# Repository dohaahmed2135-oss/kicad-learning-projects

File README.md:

# KiCad Learning Projects

Welcome to my **KiCad Learning Projects** repository!

This repository documents my journey of learning **PCB design** using KiCad through a series of practical hardware projects. Each project has helped me build a stronger understanding of schematic design, PCB layout, component placement, routing, and hardware documentation.

---

## Skills Developed

* Schematic Capture
* PCB Layout & Routing
* Component & Footprint Selection
* Electrical Rule Check (ERC)
* Design Rule Check (DRC)
* Power & Signal Routing
* PCB Visualization
* Embedded Hardware Design
* GitHub

---

# Projects

## 01 - 12V AC to DC Converter

Designed a PCB for converting AC voltage to a regulated DC output while learning the complete PCB design workflow in KiCad.

<table>
<tr>
<td align="center">
<br>
<b>PCB Layout</b>
</td>

<td align="center">
<br>
<b>3D Front View</b>
</td>
</tr>
</table>

---

## 02 - Motor Driver

Designed a motor driver PCB to practice component placement, power routing, and PCB organization for embedded applications.

<table>
<tr>
<td align="center">
<br>
<b>PCB Layout</b>
</td>

<td align="center">
<br>
<b>3D Front View</b>
</td>
</tr>
</table>

---

## 03 - STM32 GPS Tracker with SIM808

Designed an STM32-based GPS tracking PCB integrating the SIM808 GSM/GPRS and GPS module.

<table>
<tr>
<td align="center">
<br>
<b>PCB Front Layout</b>
</td>

<td align="center">
<br>
<b>3D Front View</b>
</td>
</tr>
</table>

---

## 04 - STM32 Bluetooth 

Designed a custom STM32 Bluetooth development board to gain experience with wireless embedded hardware design. This project focused on Bluetooth module integration, PCB placement, routing, and overall board organization.

<table>
<tr>
<td align="center">
<br>
<b>PCB Layout</b>
</td>

<td align="center">
<br>
<b>3D Front View</b>
</td>
</tr>
</table>

---

## 05 - ESP32 S3 IOT Testboard

Designed a four-layer ESP32-S3 IoT development board featuring sensor interfaces and a QWIIC connector. This project provided practical experience with multilayer PCB design, power distribution, and high-density routing techniques.

<table>
<tr>
<td align="center">
<br>
<b>PCB Front Layout</b>
</td>

<td align="center">
<br>
<b>3D Front View</b>
</td>
</tr>
</table>

# Learning Goal

The purpose of this repository is to document my progress in PCB design while building a strong foundation in embedded systems and hardware engineering.

My long-term goal is to design complete embedded and robotics systems by combining PCB design, embedded software, CAD, and robotics.

# Acknowledgements

The projects in this repository were completed as part of my PCB design learning journey using the following educational resources:

Ampnics – Master KiCad With Projects (Projects 01–03)

Phil's Lab – KiCad 7 STM32 Bluetooth Hardware Design (Project 04)

KiCad 9: Design an ESP32-S3 IoT 4-layer PCB with Sensor and QWIIC Interface – Complete Guide (Project 05)

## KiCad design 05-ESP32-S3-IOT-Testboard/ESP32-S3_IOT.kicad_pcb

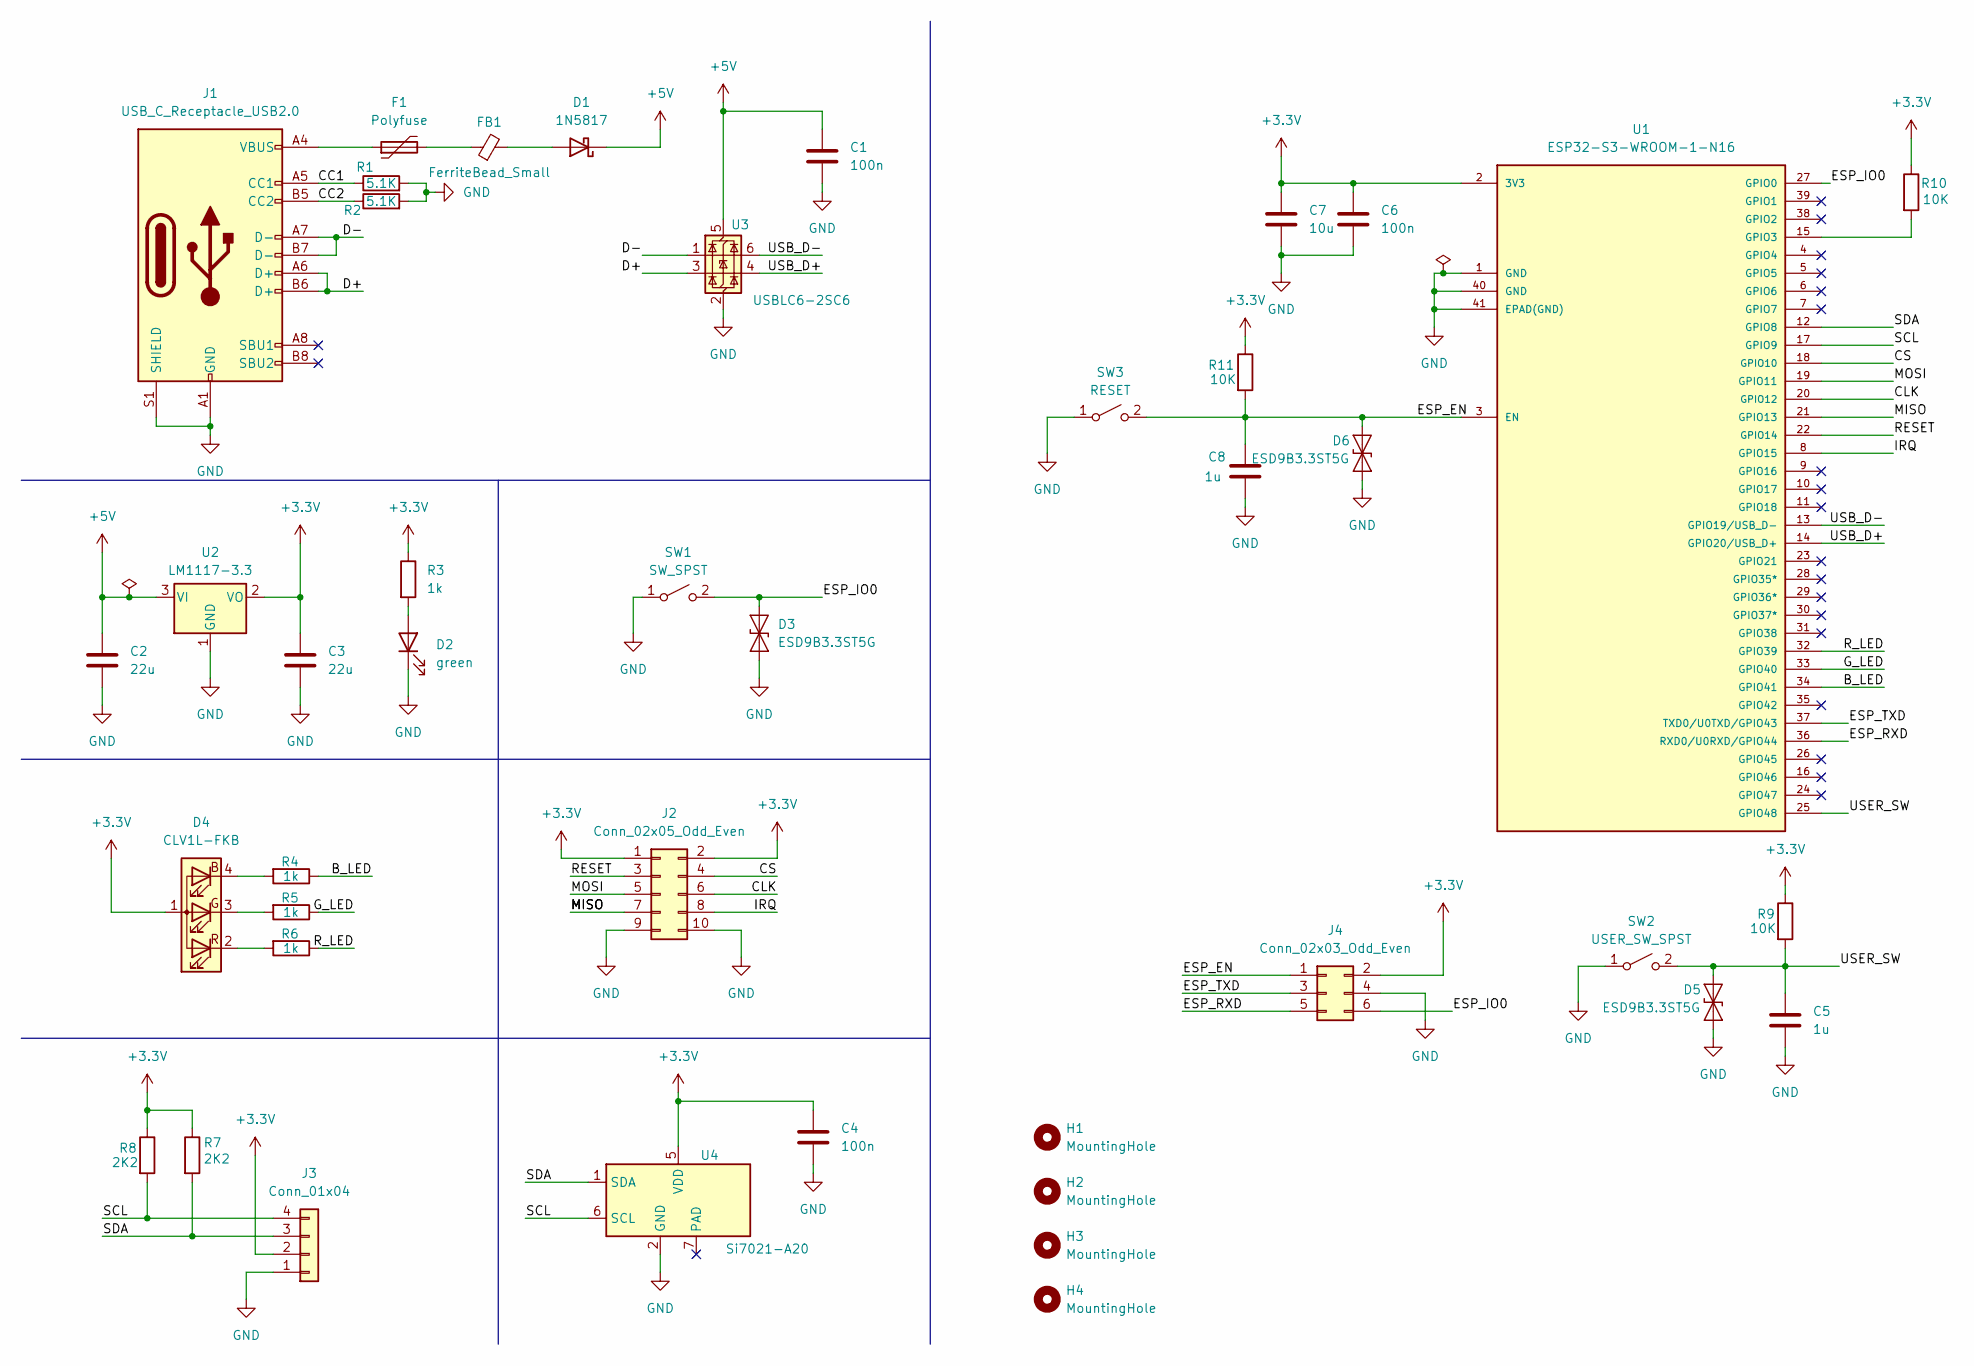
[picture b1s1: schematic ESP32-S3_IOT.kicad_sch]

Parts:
C1, C4, C6: 100n; C_0402_1005Metric_Pad0.74x0.62mm_HandSolder
C2, C3: 22u; C_0805_2012Metric
C5, C8: 1u; C_0603_1608Metric
C7: 10u; C_0603_1608Metric
D1: 1N5817; D_SOD-123
D2: green; LED_0603_1608Metric
D3, D5, D6: ESD9B3.3ST5G; D_SOD-923
D4: CLV1L-FKB; LED_Cree-PLCC4_3.2x2.8mm_CCW
F1: Polyfuse; Fuse_1206_3216Metric
FB1: FerriteBead_Small; L_0805_2012Metric
H1, H2, H3, H4: MountingHole; MountingHole_3.2mm_M3
J1: USB_C_Receptacle_USB2.0; USB_C_Receptacle_HRO_TYPE-C-31-M-12
J2: Conn_02x05_Odd_Even; PinHeader_2x05_P2.54mm_Vertical
J3: Conn_01x04; JST_XH_S4B-XH-A-1_1x04_P2.50mm_Horizontal
J4: Conn_02x03_Odd_Even; PinHeader_2x03_P2.54mm_Vertical
R1, R2: 5.1K; R_0402_1005Metric
R3, R4, R5, R6: 1k; R_0402_1005Metric
R7, R8: 2K2; R_0402_1005Metric
R9, R10, R11: 10K; R_0402_1005Metric
SW1: SW_SPST; SW_SPST_B3U-1000P
SW2: USER_SW_SPST; SW_Tactile_SPST_Angled_PTS645Vx31-2LFS
SW3: RESET; SW_SPST_B3U-1000P
U1: ESP32-S3-WROOM-1-N16; ESP32-S3-WROOM-1
U2: LM1117-3.3; SOT-223-3_TabPin2
U3: USBLC6-2SC6; SOT-23-6
U4: Si7021-A20; DFN-6-1EP_3x3mm_P1mm_EP1.5x2.4mm

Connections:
+3.3V: C3.1, C4.1, C6.1, C7.1, D4.1 (A), J2.1, J2.2, J3.2, J4.2, R3.1, R7.1, R8.1, R9.1, R10.1, R11.1, U1.2 (3V3), U2.2 (VO), U4.5 (VDD)
+5V: C1.1, C2.1, D1.1 (K), U2.3 (VI), U3.5 (VBUS)
/B_LED: R4.1, U1.34 (GPIO41)
/CC1: J1.A5 (CC1), R1.1
/CC2: J1.B5 (CC2), R2.1
/CLK: J2.6, U1.20 (GPIO12)
/CS: J2.4, U1.18 (GPIO10)
/D+: J1.A6 (D+), J1.B6 (D+), U3.3 (I/O2)
/D-: J1.A7 (D-), J1.B7 (D-), U3.1 (I/O1)
/ESP_EN: C8.1, D6.2 (A2), J4.1, R11.2, SW3.2 (B), U1.3 (EN); also elsewhere on the board
/ESP_IO0: D3.2 (A2), J4.6, SW1.2 (B), U1.27 (GPIO0); also elsewhere on the board
/ESP_RXD: J4.5, U1.36 (RXD0/U0RXD/GPIO44)
/ESP_TXD: J4.3, U1.37 (TXD0/U0TXD/GPIO43)
/G_LED: R5.1, U1.33 (GPIO40)
/IRQ: J2.8, U1.8 (GPIO15)
/MISO: J2.7, U1.21 (GPIO13)
/MOSI: J2.5, U1.19 (GPIO11)
/RESET: J2.3, U1.22 (GPIO14)
/R_LED: R6.1, U1.32 (GPIO39)
/SCL: J3.4, R8.2, U1.17 (GPIO9), U4.6 (SCL)
/SDA: J3.3, R7.2, U1.12 (GPIO8), U4.1 (SDA)
/USB_D+: U1.14 (GPIO20/USB_D+), U3.4 (I/O2)
/USB_D-: U1.13 (GPIO19/USB_D-), U3.6 (I/O1)
/USER_SW: C5.1, D5.2 (A2), R9.2, SW2.2 (B), U1.25 (GPIO48); also elsewhere on the board
GND: C1.2, C2.2, C3.2, C4.2, C5.2, C6.2, C7.2, C8.2, D2.1 (K), D3.1 (A1), D5.1 (A1), D6.1 (A1), J1.A1 (GND), J1.A12 (GND), J1.B1 (GND), J1.B12 (GND), J1.S1 (SHIELD), J2.9, J2.10, J3.1, J4.4, R1.2, R2.2, SW1.1 (A), SW2.1 (A), SW3.1 (A), U1.1 (GND), U1.40 (GND), U1.41 (EPAD(GND)), U2.1 (GND), U3.2 (GND), U4.2 (GND); also elsewhere on the board
unnamed: D1.2 (A), FB1.2
unnamed: D2.2 (A), R3.2
unnamed: D4.4 (BK), R4.2
unnamed: D4.3 (GK), R5.2
unnamed: D4.2 (RK), R6.2
unnamed: F1.1, J1.A4 (VBUS), J1.A9 (VBUS), J1.B4 (VBUS), J1.B9 (VBUS)
unnamed: F1.2, FB1.1
unnamed: R10.2, U1.15 (GPIO3)

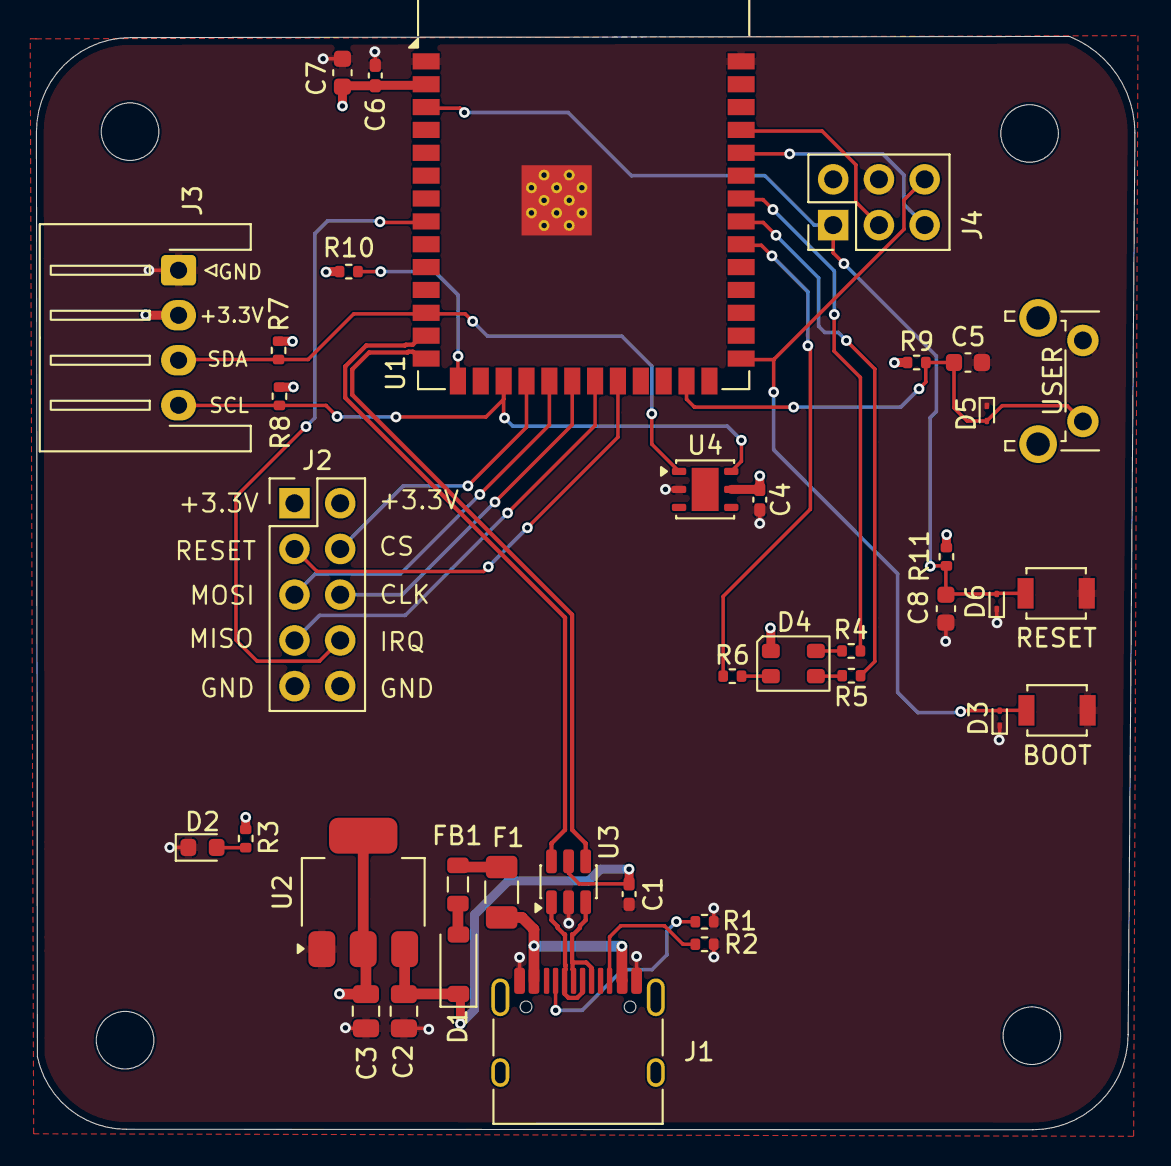
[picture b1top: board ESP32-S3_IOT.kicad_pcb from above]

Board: 4 copper layers, 61.0 x 60.7 mm, 42 parts (0 on the bottom side), 33 nets.

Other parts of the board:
BOOT: SW_SPST; SW_SPST_B3U-1000P
RESET: RESET; SW_SPST_B3U-1000P
USER: USER_SW_SPST; SW_Tactile_SPST_Angled_PTS645Vx31-2LFS

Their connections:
/ESP_EN: RESET.2 (B); also elsewhere on the board
/ESP_IO0: BOOT.2 (B); also elsewhere on the board
/USER_SW: USER.2 (B); also elsewhere on the board
GND: BOOT.1 (A), RESET.1 (A), USER.1 (A); also elsewhere on the board

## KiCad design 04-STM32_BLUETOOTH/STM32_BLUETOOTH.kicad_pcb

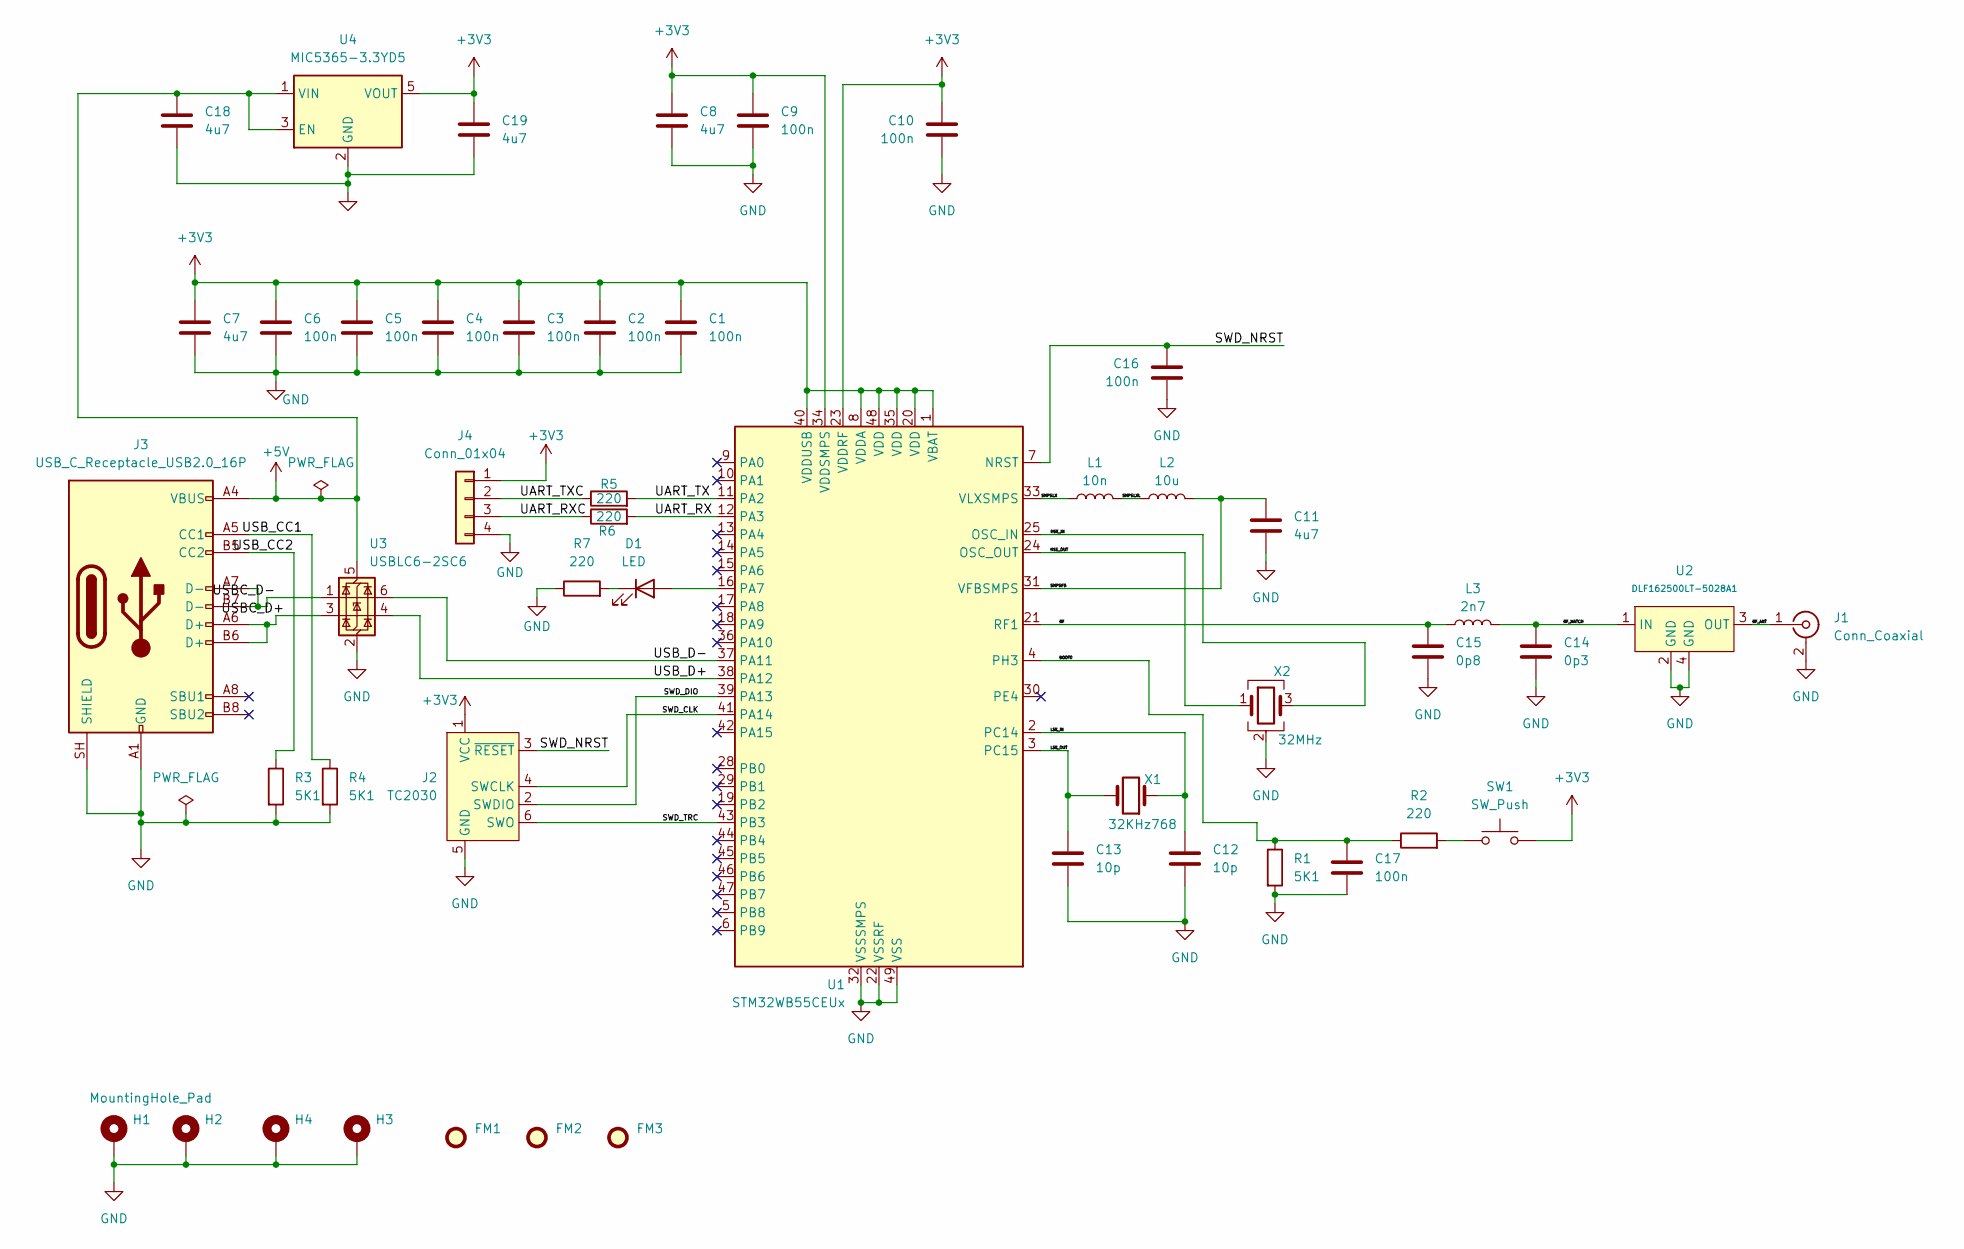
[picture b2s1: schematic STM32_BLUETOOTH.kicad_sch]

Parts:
C1, C2, C3, C4, C5, C6, C9, C10, C16, C17: 100n; C_0402_1005Metric
C7, C8, C11, C18, C19: 4u7; C_0603_1608Metric
C12, C13: 10p; C_0402_1005Metric
C14: 0p3; C_0402_1005Metric
C15: 0p8; C_0402_1005Metric
D1: LED; LED_0402_1005Metric
FM1, FM2, FM3: Fiducial; Fiducial_1mm_Mask2mm
H1, H2, H3, H4: MountingHole_Pad; MountingHole_2.2mm_M2_Pad_Via
J1: Conn_Coaxial; U.FL_Hirose_U.FL-R-SMT-1_Vertical
J2: TC2030; Tag-Connect_TC2030-IDC-FP_2x03_P1.27mm_Vertical
J3: USB_C_Receptacle_USB2.0_16P; USB_C_Receptacle_GCT_USB4105-xx-A_16P_TopMnt_Horizontal
J4: Conn_01x04; Molex_PicoBlade_53048-0410_1x04_P1.25mm_Horizontal
L1: 10n; L_0402_1005Metric
L2: 10u; L_0805_2012Metric
L3: 2n7; L_0402_1005Metric
R1, R3, R4: 5K1; R_0402_1005Metric
R2, R5, R6, R7: 220; R_0402_1005Metric
SW1: SW_Push; SW_SPST_CK_RS282G05A3
U1: STM32WB55CEUx; QFN-48-1EP_7x7mm_P0.5mm_EP5.6x5.6mm
U2: DLF162500LT-5028A1; FIL_DEA160915LT-1169
U3: USBLC6-2SC6; SOT-23-6
U4: MIC5365-3.3YD5; TSOT-23-5
X1: 32KHz768; Crystal_SMD_2012-2Pin_2.0x1.2mm
X2: 32MHz; Crystal_SMD_2016-4Pin_2.0x1.6mm

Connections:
+3V3: C1.1, C2.1, C3.1, C4.1, C5.1, C6.1, C7.1, C8.1, C9.1, C10.1, C19.1, J2.1 (VCC), J4.1, SW1.2, U1.1 (VBAT), U1.8 (VDDA), U1.20 (VDD), U1.23 (VDDRF), U1.34 (VDDSMPS), U1.35 (VDD), U1.40 (VDDUSB), U1.48 (VDD), U4.5 (VOUT)
+5V: C18.1, J3.A4 (VBUS), J3.A9 (VBUS), J3.B4 (VBUS), J3.B9 (VBUS), U3.5 (VBUS), U4.1 (VIN), U4.3 (EN)
/BOOT0: C17.1, R1.1, R2.1, U1.4 (PH3)
/HSE_IN: U1.25 (OSC_IN), X2.3
/HSE_OUT: U1.24 (OSC_OUT), X2.1
/LSE_IN: C12.1, U1.2 (PC14), X1.1
/LSE_OUT: C13.1, U1.3 (PC15), X1.2
/RF: C15.1, L3.1, U1.21 (RF1)
/RF_ANT: J1.1 (In), U2.3 (OUT)
/RF_MATCH: C14.1, L3.2, U2.1 (IN)
/SMPSFB: C11.1, L2.2, U1.31 (VFBSMPS)
/SMPSLX: L1.1, U1.33 (VLXSMPS)
/SMPSLXL: L1.2, L2.1
/SWD_CLK: J2.4 (SWCLK), U1.41 (PA14)
/SWD_DIO: J2.2 (SWDIO), U1.39 (PA13)
/SWD_NRST: C16.1, J2.3 (~RESET), U1.7 (NRST)
/SWD_TRC: J2.6 (SWO), U1.43 (PB3)
/UART_RX: R6.2, U1.12 (PA3)
/UART_RXC: J4.3, R6.1
/UART_TX: R5.2, U1.11 (PA2)
/UART_TXC: J4.2, R5.1
/USBC_D+: J3.A6 (D+), J3.B6 (D+), U3.3 (I/O2)
/USBC_D-: J3.A7 (D-), J3.B7 (D-), U3.1 (I/O1)
/USB_CC1: J3.A5 (CC1), R4.1
/USB_CC2: J3.B5 (CC2), R3.1
/USB_D+: U1.38 (PA12), U3.4 (I/O2)
/USB_D-: U1.37 (PA11), U3.6 (I/O1)
GND: C1.2, C2.2, C3.2, C4.2, C5.2, C6.2, C7.2, C8.2, C9.2, C10.2, C11.2, C12.2, C13.2, C14.2, C15.2, C16.2, C17.2, C18.2, C19.2, H1.1 (1_1), H2.1 (1_1), H3.1 (1_1), H4.1 (1_1), J1.2 (Ext), J2.5 (GND), J3.A1 (GND), J3.A12 (GND), J3.B1 (GND), J3.B12 (GND), J3.SH (SHIELD), J4.4, R1.2, R3.2, R4.2, R7.1, U1.22 (VSSRF), U1.32 (VSSSMPS), U1.49 (VSS), U2.2 (GND), U2.4 (GND), U3.2 (GND), U4.2 (GND), X2.2 (G), X2.4 (G)
unnamed: D1.2 (A), U1.16 (PA7)
unnamed: D1.1 (K), R7.2
unnamed: R2.2, SW1.1

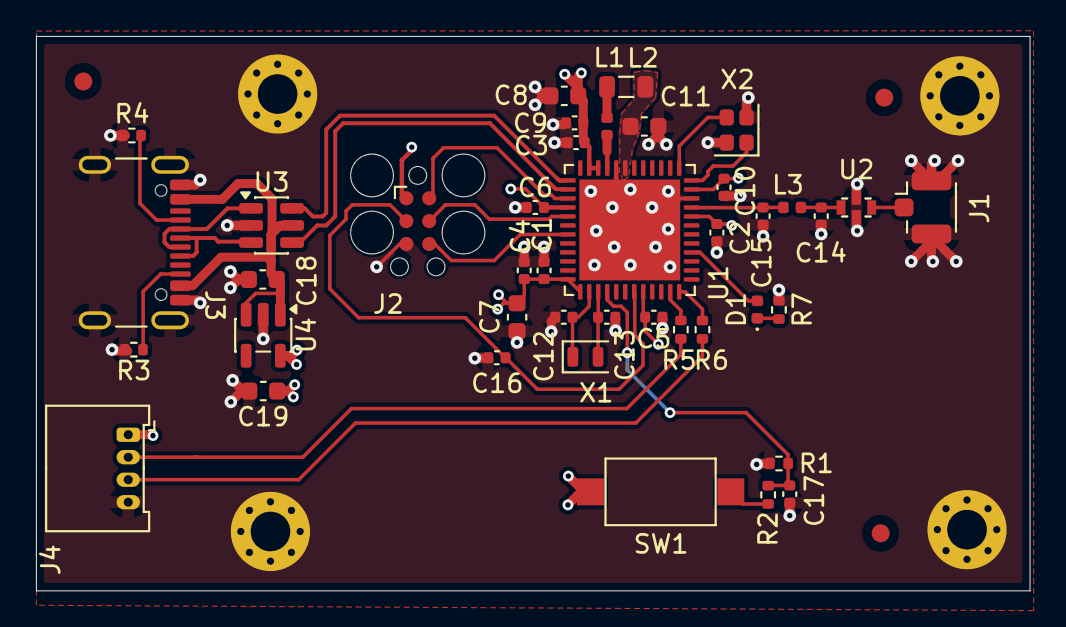
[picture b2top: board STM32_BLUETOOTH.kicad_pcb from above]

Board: 4 copper layers, 55.2 x 30.8 mm, 48 parts (0 on the bottom side), 31 nets.

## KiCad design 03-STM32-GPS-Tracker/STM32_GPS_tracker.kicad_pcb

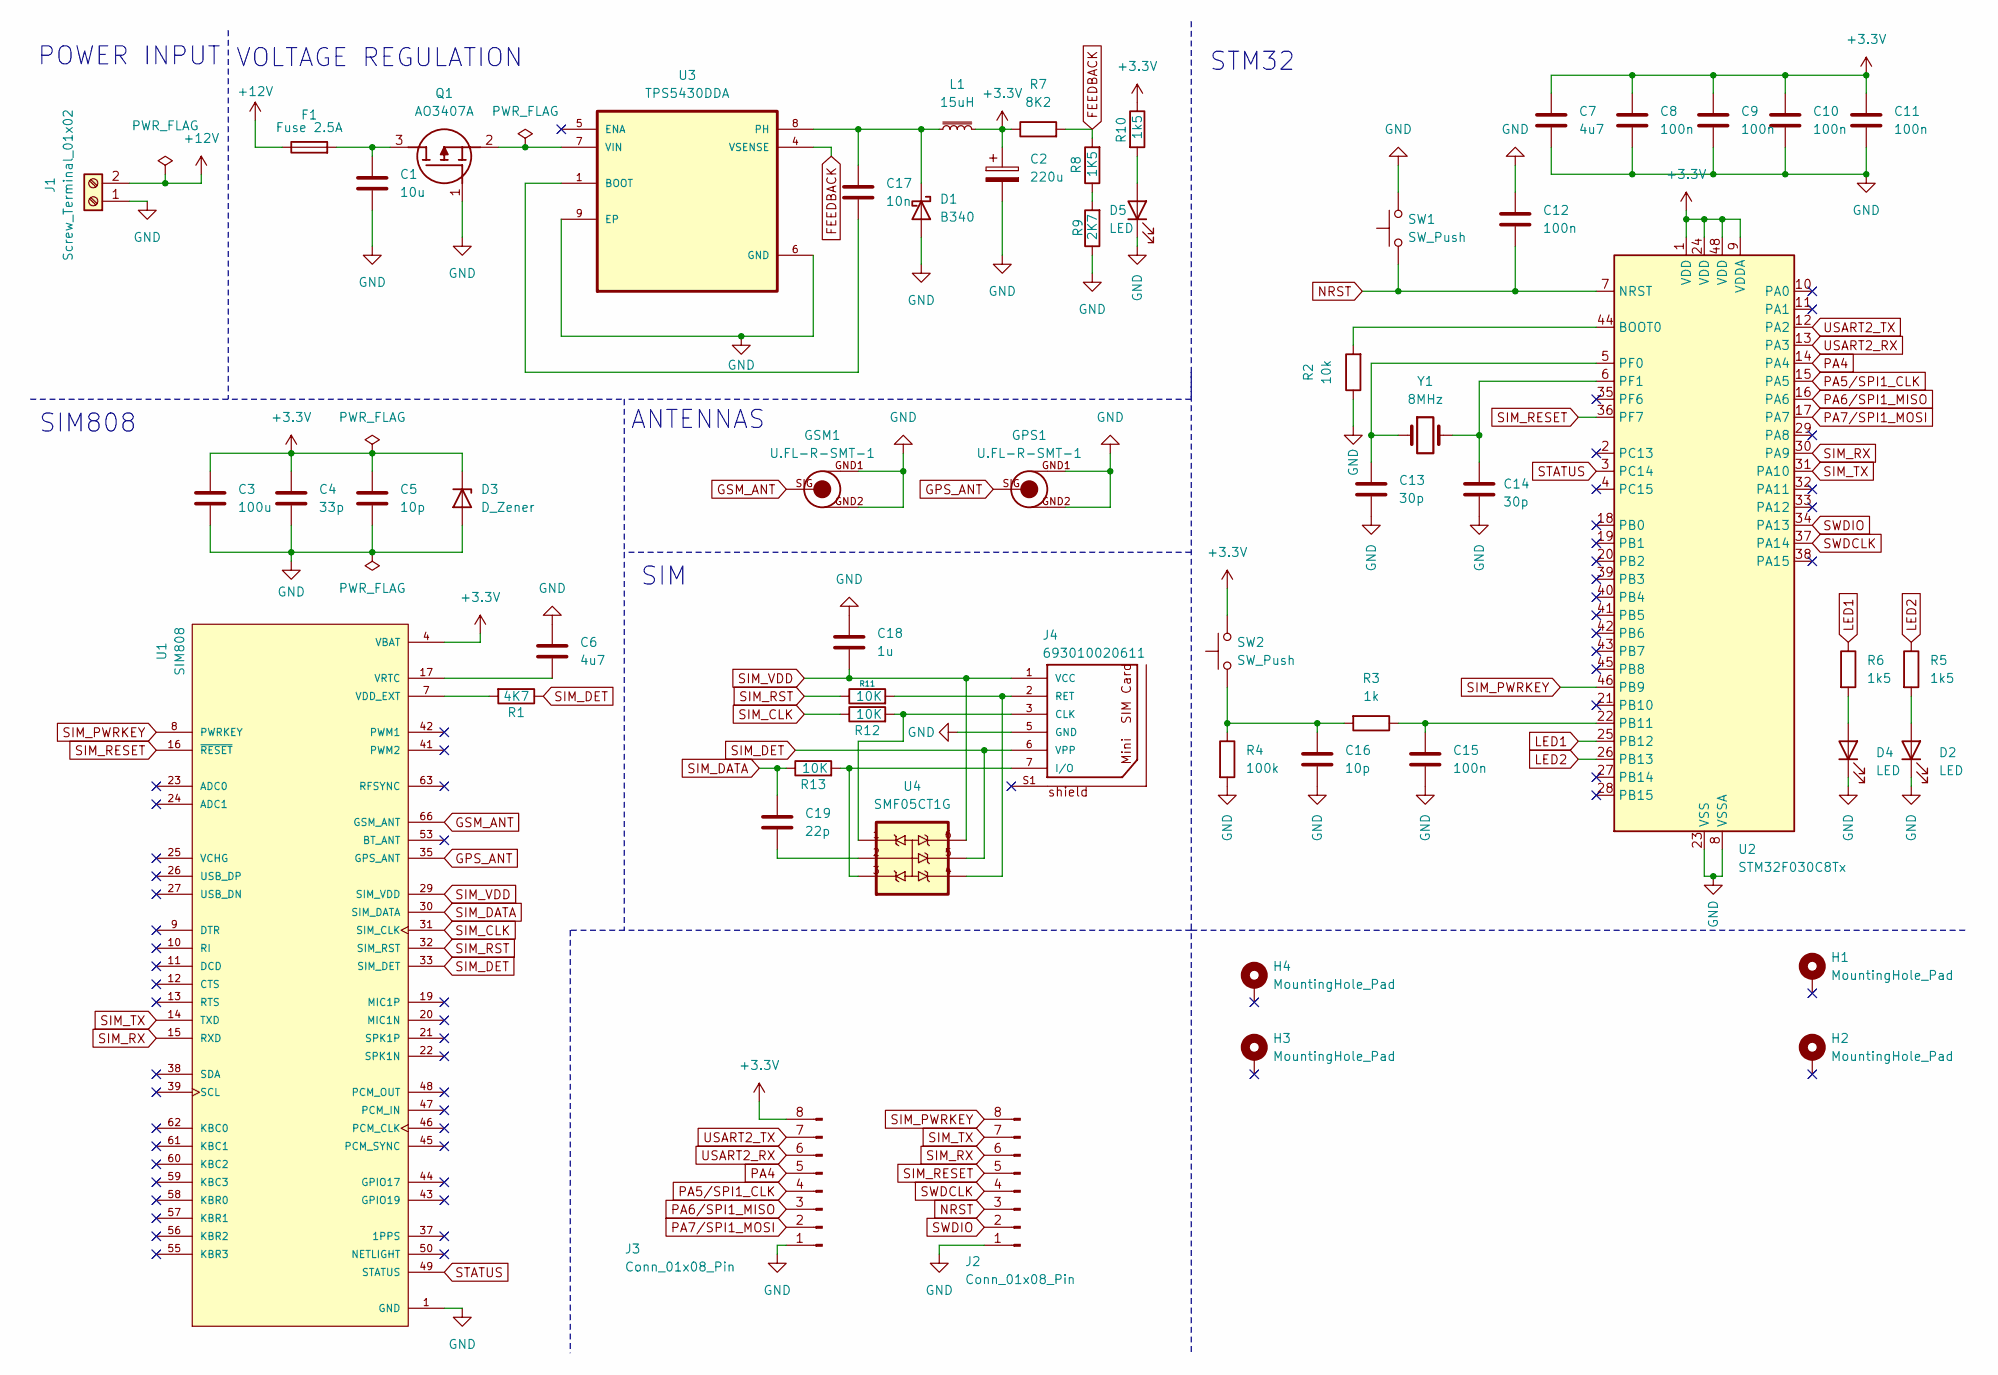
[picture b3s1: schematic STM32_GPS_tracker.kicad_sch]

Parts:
C1: 10u; C_0805_2012Metric
C2: 220u; CP_EIA-7343-15_Kemet-W
C3: 100u; C_0805_2012Metric
C4: 33p; C_0805_2012Metric
C5, C16: 10p; C_0805_2012Metric
C6, C7: 4u7; C_0805_2012Metric
C8, C9, C10, C11, C12, C15: 100n; C_0805_2012Metric
C13, C14: 30p; C_0805_2012Metric
C17: 10n; C_0805_2012Metric
C18: 1u; C_0805_2012Metric
C19: 22p; C_0805_2012Metric
D1: B340; D_SMC
D2, D4, D5: LED; LED_0805_2012Metric
D3: D_Zener; D_0805_2012Metric
F1: Fuse 2.5A; Fuse_0402_1005Metric
GPS1: U.FL-R-SMT-1
GSM1: U.FL-R-SMT-1
H1, H2, H3, H4: MountingHole_Pad; MountingHole_2.2mm_M2_Pad_Via
J1: Screw_Terminal_01x02; TerminalBlock_MetzConnect_Type073_RT02602HBLU_1x02_P5.08mm_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
J2, J3: Conn_01x08_Pin; PinHeader_1x08_P2.54mm_Vertical
J4: 693010020611
L1: 15uH; L_10.4x10.4_H4.8
Q1: AO3407A; SOT95P280X125-3N; Manufacturer_Part_Number AO3407A
R1: 4K7; R_0805_2012Metric
R2: 10k; R_0805_2012Metric
R3: 1k; R_0805_2012Metric
R4: 100k; R_0805_2012Metric
R5, R6, R10: 1k5; R_0805_2012Metric
R7: 8K2; R_0805_2012Metric
R8: 1K5; R_0805_2012Metric
R9: 2K7; R_0805_2012Metric
R11, R12, R13: 10K; R_0805_2012Metric
SW1, SW2: SW_Push; SW_Push_1P1T_NO_CK_KSC6xxJ
U1: SIM808; XCVR_SIM808; PARTREV 1.03
U2: STM32F030C8Tx; LQFP-48_7x7mm_P0.5mm
U3: TPS5430DDA; VREG_LM5017MR_NOPB
U4: SMF05CT1G; SOT65P210X110-6N
Y1: 8MHz; Crystal_SMD_5032-2Pin_5.0x3.2mm

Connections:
+3.3V: C2.1, C3.1, C4.1, C5.1, C7.1, C8.1, C9.1, C10.1, C11.1, D3.1 (K), J3.8, L1.2, R7.1, R10.1, SW2.2, U1.4 (VBAT), U1.5 (VBAT), U1.6 (VBAT), U2.1 (VDD), U2.9 (VDDA), U2.24 (VDD), U2.48 (VDD); also elsewhere on the board
+12V: F1.1, J1.2
FEEDBACK: R7.2, R8.2, U3.4 (VSENSE)
GND: C1.2, C2.2, C3.2, C4.2, C5.2, C6.1, C7.2, C8.2, C9.2, C10.2, C11.2, C12.1, C13.2, C14.2, C15.2, C16.2, C18.1, D1.2 (A), D2.1 (K), D3.2 (A), D4.1 (K), D5.1 (K), GPS1.GND1, GPS1.GND2, GSM1.GND1, GSM1.GND2, J1.1, J2.1, J3.1, J4.5 (GND), Q1.1 (G), R2.1, R4.2, R9.1, SW1.2, U1.1 (GND), U1.2 (GND), U1.3 (GND), U1.18 (GND), U1.28 (GND), U1.34 (GND), U1.36 (GND), U1.40 (GND), U1.51 (GND), U1.52 (GND), U1.54 (GND), U1.64 (GND), U1.65 (GND), U1.67 (GND), U1.68 (GND), U2.8 (VSSA), U2.23 (VSS), U2.47 (VSS), U3.6 (GND), U3.9 (EP); also elsewhere on the board
GPS_ANT: GPS1.SIG, U1.35 (GPS_ANT)
GSM_ANT: GSM1.SIG, U1.66 (GSM_ANT)
LED1: R6.1, U2.25 (PB12)
LED2: R5.1, U2.26 (PB13)
NRST: C12.2, J2.3, SW1.1, U2.7 (NRST); also elsewhere on the board
unnamed 9: C16.1, R3.2, R4.1, SW2.1; also elsewhere on the board
unnamed: C19.2, U4.2
unnamed: C17.1, D1.1 (K), L1.1, U3.8 (PH)
unnamed: D2.2 (A), R5.2
unnamed: D4.2 (A), R6.2
unnamed: D5.2 (A), R10.2
unnamed 15: J4.3 (CLK), R12.2, U4.1; also elsewhere on the board
unnamed 16: J4.7 (I/O), R13.2, U4.3; also elsewhere on the board
unnamed: J4.S1, J4.S2, J4.S3, J4.S4
unnamed 18: J4.2 (RET), R11.2, U4.4; also elsewhere on the board
unnamed: C1.1, F1.2, Q1.3 (D)
unnamed: Q1.2 (S), U3.7 (VIN)
unnamed: R8.1, R9.2
unnamed: R1.2, U1.7 (VDD_EXT)
unnamed: C6.2, U1.17 (VRTC)
unnamed: R2.2, U2.44 (BOOT0)
unnamed: C15.1, R3.1, U2.22 (PB11)
unnamed: C13.1, U2.5 (PF0), Y1.1
unnamed: C14.1, U2.6 (PF1), Y1.2
unnamed: C17.2, U3.1 (BOOT)
PA4: J3.5, U2.14 (PA4)
PA5/SPI1_CLK: J3.4, U2.15 (PA5)
PA6/SPI1_MISO: J3.3, U2.16 (PA6)
PA7/SPI1_MOSI: J3.2, U2.17 (PA7)
SIM_CLK: R12.1, U1.31 (SIM_CLK)
SIM_DATA: C19.1, R13.1, U1.30 (SIM_DATA)
SIM_DET: J4.6 (VPP), R1.1, U1.33 (SIM_DET), U4.5; also elsewhere on the board
SIM_PWRKEY: J2.8, U1.8 (PWRKEY), U2.46 (PB9)
SIM_RESET: J2.5, U1.16 (~RESET), U2.36 (PF7)
SIM_RST: R11.1, U1.32 (SIM_RST)
SIM_RX: J2.6, U1.15 (RXD), U2.30 (PA9)
SIM_TX: J2.7, U1.14 (TXD), U2.31 (PA10)
SIM_VDD: C18.2, J4.1 (VCC), U1.29 (SIM_VDD), U4.6; also elsewhere on the board
STATUS: U1.49 (STATUS), U2.3 (PC14)
SWDCLK: J2.4, U2.37 (PA14)
SWDIO: J2.2, U2.34 (PA13)
USART2_RX: J3.6, U2.13 (PA3)
USART2_TX: J3.7, U2.12 (PA2)

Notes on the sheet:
VOLTAGE REGULATION
POWER INPUT
ANTENNAS
SIM808
SIM
STM32

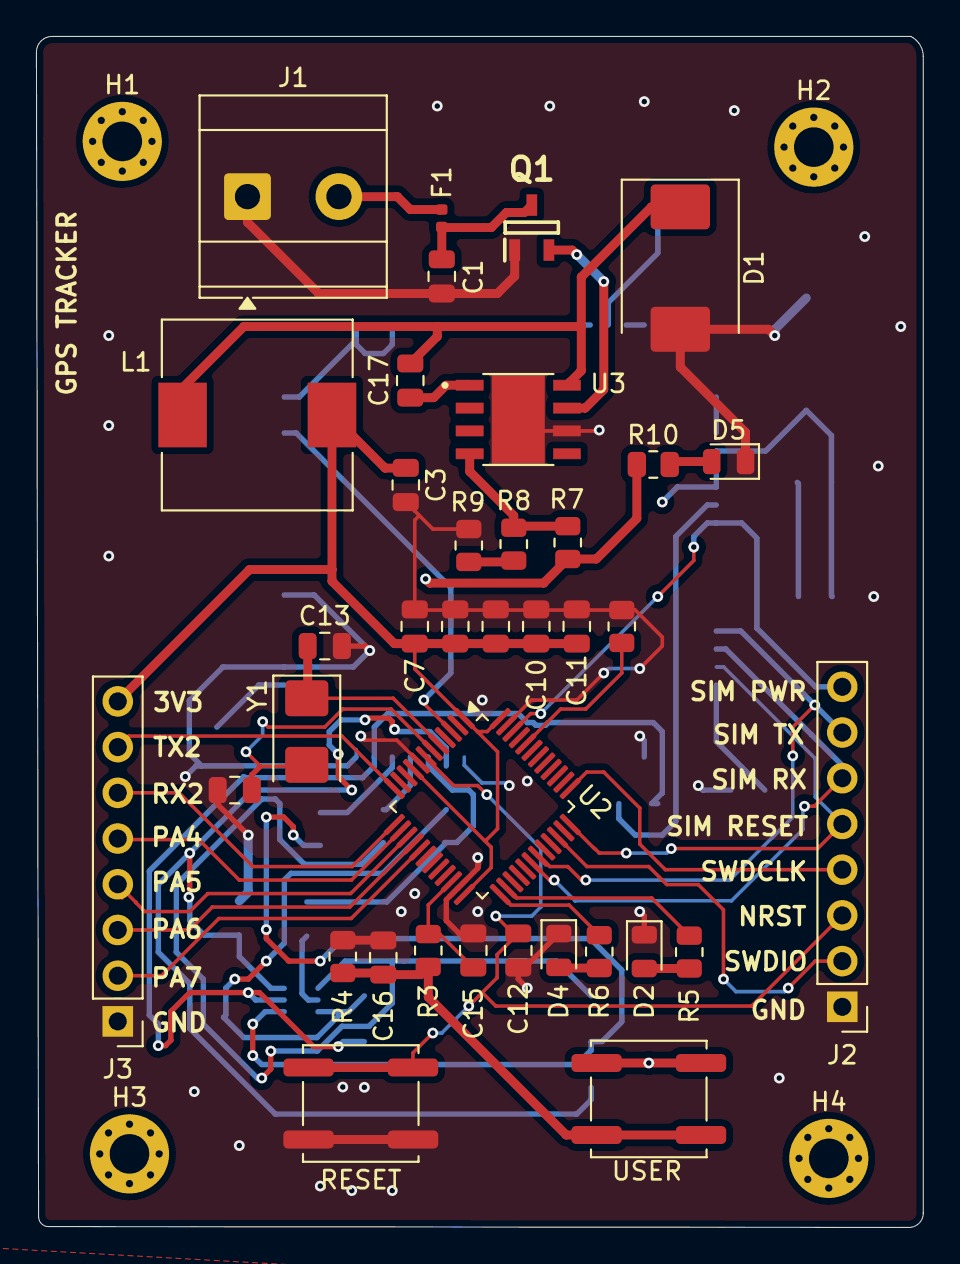
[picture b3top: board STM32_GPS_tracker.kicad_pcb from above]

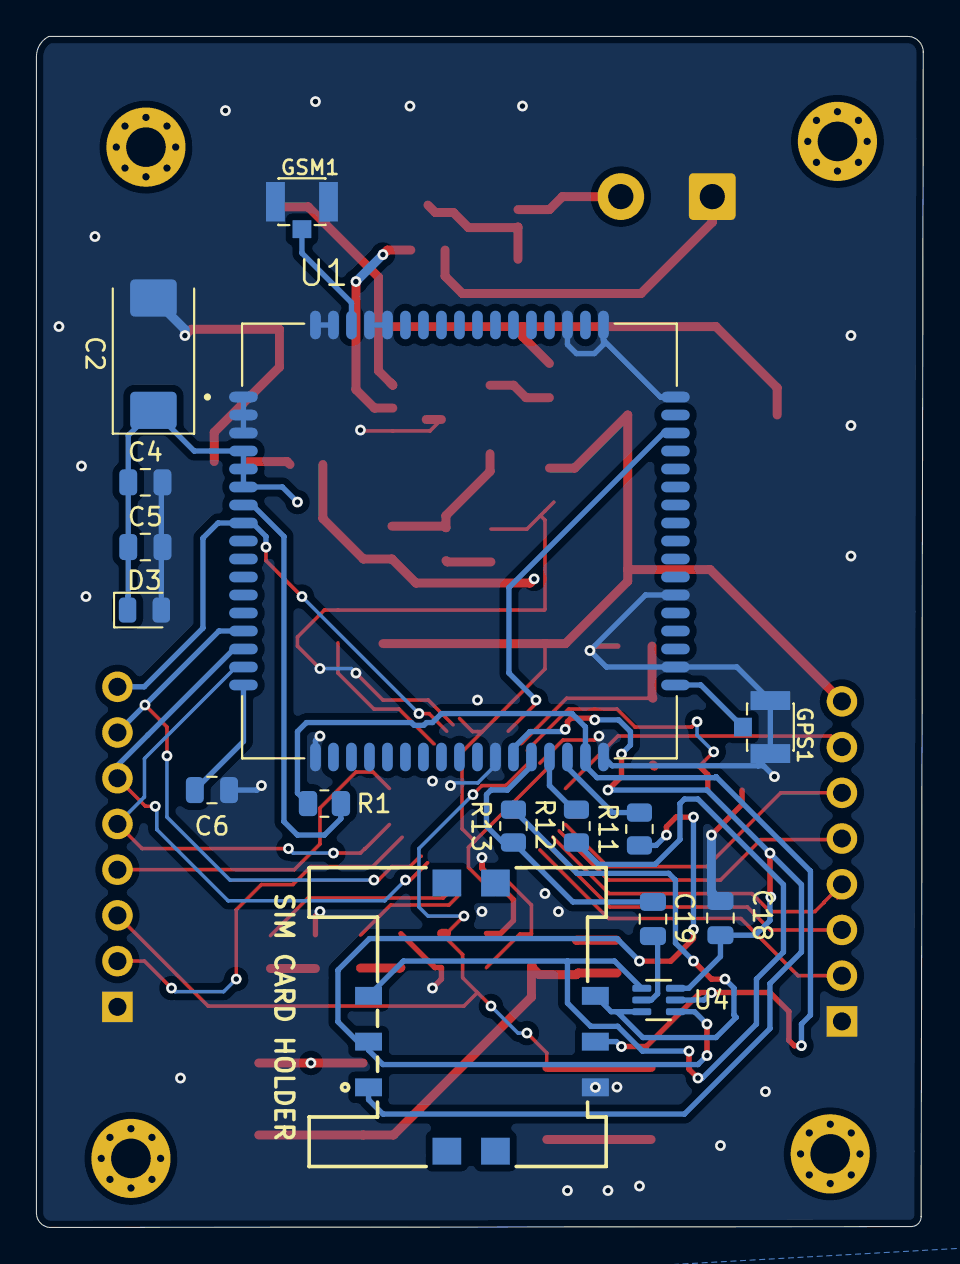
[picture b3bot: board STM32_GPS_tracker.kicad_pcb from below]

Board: 4 copper layers, 49.3 x 66.2 mm, 57 parts (16 on the bottom side), 46 nets.

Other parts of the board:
RESET: SW_Push; SW_Push_1P1T_NO_CK_KSC6xxJ
SIM CARD HOLDER: 693010020611
USER: SW_Push; SW_Push_1P1T_NO_CK_KSC6xxJ

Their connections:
+3.3V: USER.2; also elsewhere on the board
GND: RESET.2, SIM CARD HOLDER.5 (GND); also elsewhere on the board
NRST: RESET.1; also elsewhere on the board
unnamed 9: USER.1; also elsewhere on the board
unnamed 15: SIM CARD HOLDER.3 (CLK); also elsewhere on the board
unnamed 16: SIM CARD HOLDER.7 (I/O); also elsewhere on the board
unnamed 18: SIM CARD HOLDER.2 (RET); also elsewhere on the board
SIM_DET: SIM CARD HOLDER.6 (VPP); also elsewhere on the board
SIM_VDD: SIM CARD HOLDER.1 (VCC); also elsewhere on the board

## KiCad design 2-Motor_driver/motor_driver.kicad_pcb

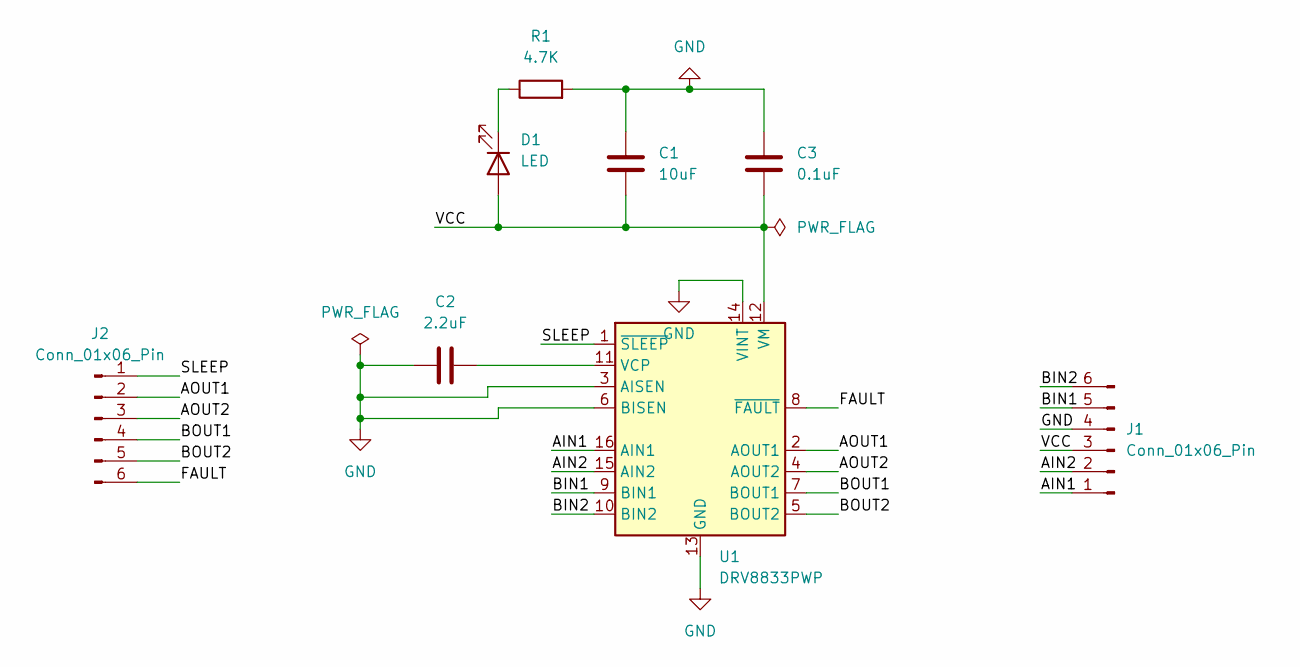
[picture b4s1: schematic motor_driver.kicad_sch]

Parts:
C1: 10uF; CP_EIA-3528-15_AVX-H
C2: 2.2uF; C_0805_2012Metric
C3: 0.1uF; C_0805_2012Metric
D1: LED; LED_0805_2012Metric
J1, J2: Conn_01x06_Pin; PinHeader_1x06_P2.54mm_Vertical
R1: 4.7K; R_0805_2012Metric
U1: DRV8833PWP; HTSSOP-16-1EP_4.4x5mm_P0.65mm_EP3.4x5mm_Mask2.66x2.46mm

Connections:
/AIN1: J1.1, U1.16 (AIN1)
/AIN2: J1.2, U1.15 (AIN2)
/AOUT1: J2.2, U1.2 (AOUT1)
/AOUT2: J2.3, U1.4 (AOUT2)
/BIN1: J1.5, U1.9 (BIN1)
/BIN2: J1.6, U1.10 (BIN2)
/BOUT1: J2.4, U1.7 (BOUT1)
/BOUT2: J2.5, U1.5 (BOUT2)
/FAULT: J2.6, U1.8 (~FAULT)
/SLEEP: J2.1, U1.1 (~SLEEP)
/VCC: C1.2, C3.2, D1.2 (A), J1.3, U1.12 (VM)
GND: C1.1, C2.1, C3.1, J1.4, R1.2, U1.3 (AISEN), U1.6 (BISEN), U1.13 (GND), U1.14 (VINT), U1.17 (GND)
unnamed: D1.1 (K), R1.1
unnamed: C2.2, U1.11 (VCP)

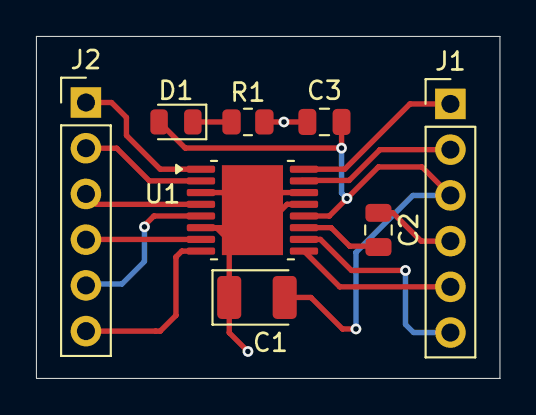
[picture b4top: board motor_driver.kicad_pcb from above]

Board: 2 copper layers, 25.8 x 19.0 mm, 8 parts (0 on the bottom side), 14 nets.

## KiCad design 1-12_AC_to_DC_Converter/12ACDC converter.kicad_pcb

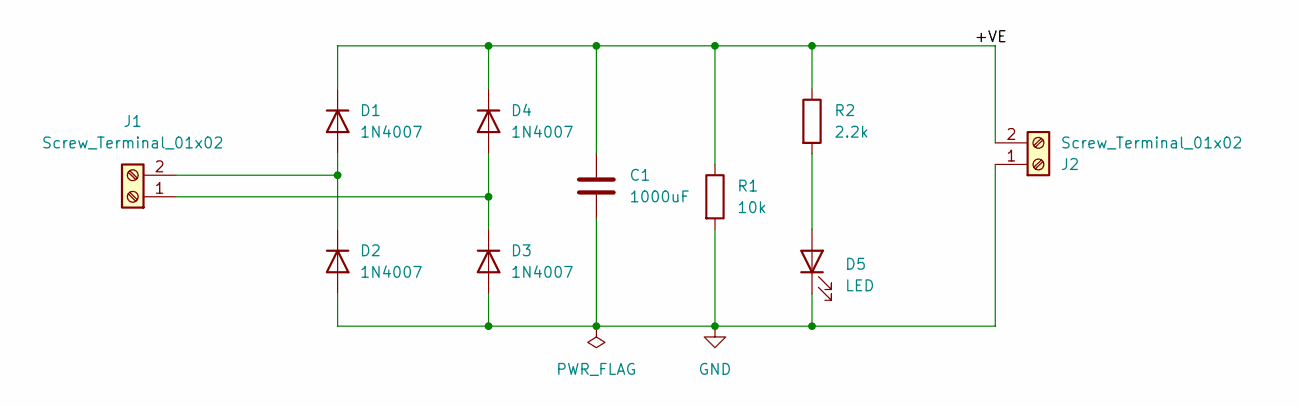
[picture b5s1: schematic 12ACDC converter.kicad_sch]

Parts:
C1: 1000uF; C_Radial_D8.0mm_H11.5mm_P3.50mm
D1, D2, D3, D4: 1N4007; D_DO-41_SOD81_P10.16mm_Horizontal
D5: LED; LED_D5.0mm
J1, J2: Screw_Terminal_01x02; TerminalBlock_MaiXu_MX126-5.0-02P_1x02_P5.00mm
R1: 10k; R_Axial_DIN0207_L6.3mm_D2.5mm_P7.62mm_Horizontal
R2: 2.2k; R_Axial_DIN0207_L6.3mm_D2.5mm_P7.62mm_Horizontal

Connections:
/+VE: C1.1, D1.1 (K), D4.1 (K), J2.2, R1.1, R2.1
GND: C1.2, D2.2 (A), D3.2 (A), D5.1 (K), J2.1, R1.2
unnamed: D1.2 (A), D2.1 (K), J1.2
unnamed: D3.1 (K), D4.2 (A), J1.1
unnamed: D5.2 (A), R2.2

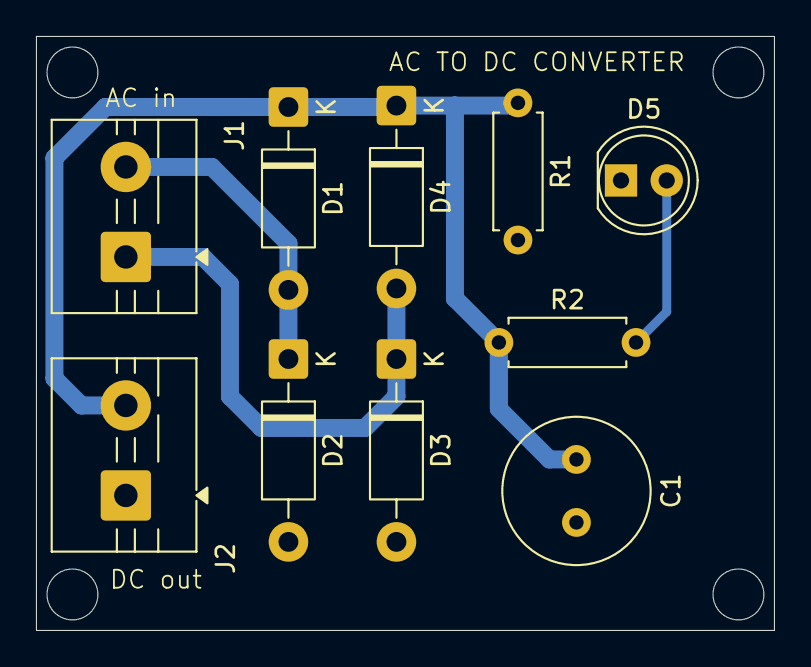
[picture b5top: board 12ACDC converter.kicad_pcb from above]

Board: 2 copper layers, 41.0 x 33.0 mm, 10 parts (0 on the bottom side), 5 nets.

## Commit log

2026-06-05 first project
2026-06-05 not needed
2026-06-19 completed
